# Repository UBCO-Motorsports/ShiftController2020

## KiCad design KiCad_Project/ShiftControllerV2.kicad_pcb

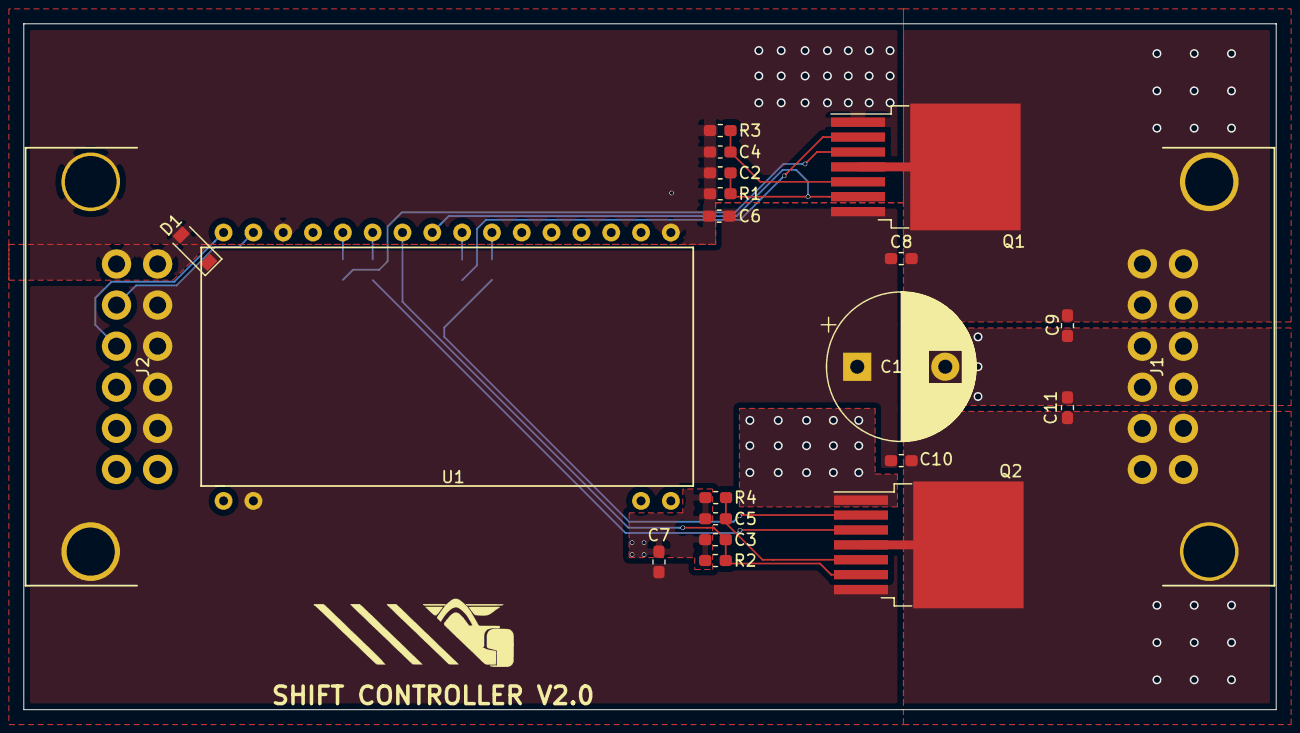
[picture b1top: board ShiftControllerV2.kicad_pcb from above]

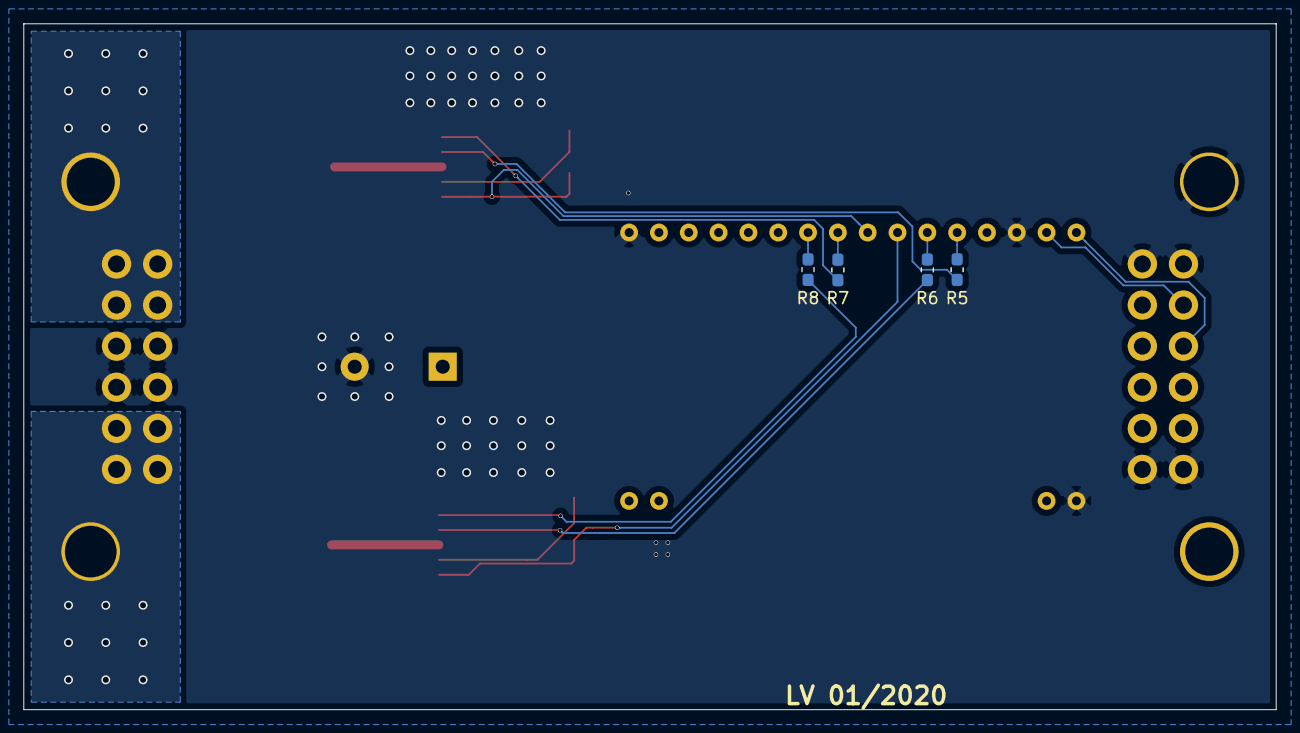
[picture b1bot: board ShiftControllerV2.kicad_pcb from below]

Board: 2 copper layers, 106.7 x 58.4 mm, 25 parts (4 on the bottom side), 18 nets.

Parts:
C1: 1000u; CP_Radial_D12.5mm_P7.50mm
C2, C3: 1n; C_0603_1608Metric_Pad1.05x0.95mm_HandSolder
C4, C5, C6, C7: 100n; C_0603_1608Metric_Pad1.05x0.95mm_HandSolder
C8, C9, C10, C11: 220n; C_0603_1608Metric_Pad1.05x0.95mm_HandSolder
D1: 30v zener; D_SOD-123
J1, J2: Conn_02x06_Top_Bottom; MX120G
Q1, Q2: BTN8982TA; TO-263-7_TabPin8
R1, R2, R3, R4: 510; R_0603_1608Metric_Pad1.05x0.95mm_HandSolder
R5, R6, R7, R8: 10k; R_0603_1608Metric_Pad1.05x0.95mm_HandSolder
U1: ControllerBoardV1; Breadboard_Center_32pin

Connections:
+12V: C1.1, C6.1, C7.1, C8.1, C10.1, D1.1, J2.2, J2.3, J2.4, J2.5, J2.13, Q1.7, Q2.7, U1.2
CANH: J2.8, U1.18
CANL: J2.9, U1.17
CURRENT1: C2.1, Q1.6, R1.1, U1.24
CURRENT2: C3.1, Q2.6, R2.1, U1.23
GND: C1.2, C2.2, C3.2, C4.2, C5.2, C6.2, C7.2, C9.2, C11.2, D1.2, J1.3, J1.4, J1.9, J1.10, J2.1, J2.6, J2.7, J2.12, J2.13, Q1.1, Q2.1, R1.2, R2.2, R3.2, R4.2, U1.1, U1.19, U1.32
IN1: Q1.2, R7.1
IN2: Q2.2, R8.1
INH1: Q1.3, R5.1
INH2: Q2.3, R6.1
unnamed: C4.1, Q1.5, R3.1
unnamed: C5.1, Q2.5, R4.1
unnamed: R5.2, U1.21
unnamed: R6.2, U1.22
unnamed: R7.2, U1.25
unnamed: R8.2, U1.26
OUT1: C8.2, C9.1, J1.5, J1.6, J1.11, J1.12, J1.13, Q1.4, Q1.8
OUT2: C10.2, C11.1, J1.1, J1.2, J1.7, J1.8, J1.13, Q2.4, Q2.8

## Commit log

2019-11-20 Added entire kicad project
2019-11-20 Added Folder for S32DS project
2019-11-20 Modified folder for S32DS project
2019-11-22 Removed .DS_Store
2019-11-25 Began planning arrangement of components
2020-01-16 Layout almost complete
2020-01-30 V1 Complete and out for manufacturing
2020-01-30 Exported Step file
2020-02-03 First code upload
    Both LPIT channels implemented. Base logic implemented. CAN filtering setup.
2020-02-13 Started hardware testing.
2020-02-15 Improvements on CAN receiving and fixed LPIT start/stop
2020-02-16 Added debug files
2020-02-16 Fixed GIT issues
2020-02-16 Fixed debug configuration naming
2020-02-16 Added include directory
2020-02-16 Removing debug configurations
2020-02-16 Fixing gitignore
